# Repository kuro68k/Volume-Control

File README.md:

# Volume-Control
USB volume control and companion app

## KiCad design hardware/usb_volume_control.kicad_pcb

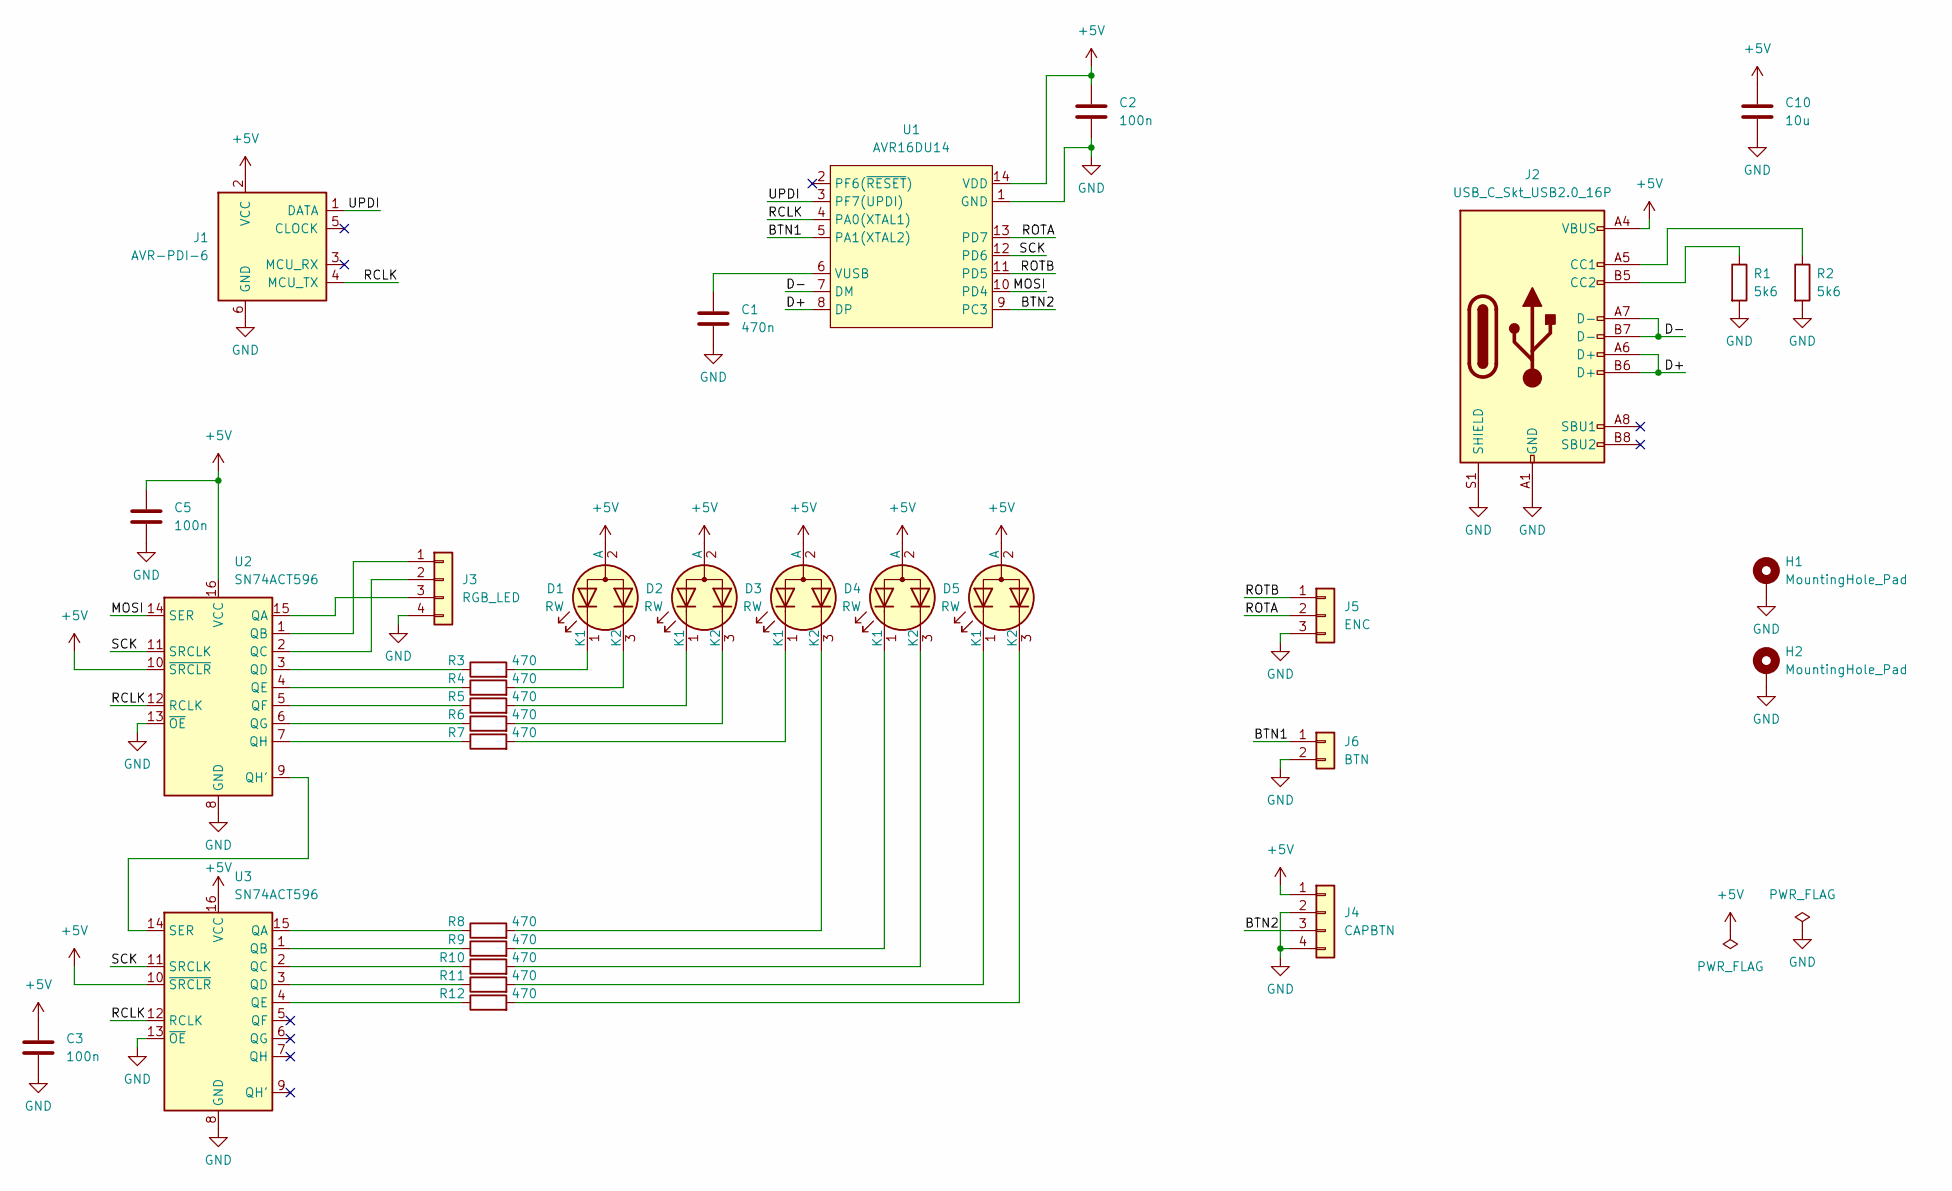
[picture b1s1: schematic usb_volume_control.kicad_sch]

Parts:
C1: 470n; C_0805_2012Metric_Pad1.18x1.45mm_HandSolder
C2, C3, C5: 100n; C_0805_2012Metric_Pad1.18x1.45mm_HandSolder
C10: 10u; C_0805_2012Metric_Pad1.18x1.45mm_HandSolder
D1, D2, D3, D4, D5: RW; LED_D3.0mm-3
H1, H2: MountingHole_Pad; MountingBracket_3.2mm_M3_Pad_tall
J1: AVR-PDI-6; PinHeader_2x03_P2.54mm_Vertical
J2: USB_C_Skt_USB2.0_16P; USB_C_Receptacle_GCT_USB4105-xx-A_16P_TopMnt_Horizontal
J3: RGB_LED; PinHeader_1x04_P2.54mm_Vertical
J4: CAPBTN; PinHeader_1x04_P2.54mm_Vertical
J5: ENC; PinHeader_1x03_P2.54mm_Vertical
J6: BTN; PinHeader_1x02_P2.54mm_Vertical
R1, R2: 5k6; R_0805_2012Metric_Pad1.20x1.40mm_HandSolder
R3, R4, R5, R6, R7, R8, R9, R10, R11, R12: 470; R_0805_2012Metric_Pad1.20x1.40mm_HandSolder
U1: AVR16DU14; SOIC-14_3.9x8.7mm_P1.27mm
U2, U3: SN74ACT596; TSSOP-16_4.4x5mm_P0.65mm

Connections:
+5V: C2.1, C3.1, C5.1, C10.1, D1.2 (A), D2.2 (A), D3.2 (A), D4.2 (A), D5.2 (A), J1.2 (VCC), J2.A4 (VBUS), J2.A9 (VBUS), J2.B4 (VBUS), J2.B9 (VBUS), J4.1, U1.14 (VDD), U2.10 (~SRCLR), U2.16 (VCC), U3.10 (~SRCLR), U3.16 (VCC)
/BTN1: J6.1, U1.5 (PA1(XTAL2))
/BTN2: J4.3, U1.9 (PC3)
/D+: J2.A6 (D+), J2.B6 (D+), U1.8 (DP)
/D-: J2.A7 (D-), J2.B7 (D-), U1.7 (DM)
/MOSI: U1.10 (PD4), U2.14 (SER)
/RCLK: J1.4 (MCU_TX), U1.4 (PA0(XTAL1)), U2.12 (RCLK), U3.12 (RCLK)
/ROTA: J5.2, U1.13 (PD7)
/ROTB: J5.1, U1.11 (PD5)
/SCK: U1.12 (PD6), U2.11 (SRCLK), U3.11 (SRCLK)
/UPDI: J1.1 (DATA), U1.3 (PF7(UPDI))
GND: C1.2, C2.2, C3.2, C5.2, C10.2, H1.1, H2.1, J1.6 (GND), J2.A1 (GND), J2.A12 (GND), J2.B1 (GND), J2.B12 (GND), J2.S1 (SHIELD), J3.4, J4.2, J4.4, J5.3, J6.2, R1.2, R2.2, U1.1 (GND), U2.8 (GND), U2.13 (~OE), U3.8 (GND), U3.13 (~OE)
unnamed: D1.1 (K1), R3.2
unnamed: D1.3 (K2), R4.2
unnamed: D2.1 (K1), R5.2
unnamed: D2.3 (K2), R6.2
unnamed: D3.1 (K1), R7.2
unnamed: D3.3 (K2), R8.2
unnamed: D4.1 (K1), R9.2
unnamed: D4.3 (K2), R10.2
unnamed: D5.1 (K1), R11.2
unnamed: D5.3 (K2), R12.2
unnamed: J2.A5 (CC1), R2.1
unnamed: J2.B5 (CC2), R1.1
unnamed: J3.1, U2.1 (QB)
unnamed: J3.2, U2.2 (QC)
unnamed: J3.3, U2.15 (QA)
unnamed: C1.1, U1.6 (VUSB)
unnamed: R3.1, U2.3 (QD)
unnamed: R4.1, U2.4 (QE)
unnamed: R5.1, U2.5 (QF)
unnamed: R6.1, U2.6 (QG)
unnamed: U2.9 (QH'), U3.14 (SER)
unnamed: R7.1, U2.7 (QH)
unnamed: R8.1, U3.15 (QA)
unnamed: R9.1, U3.1 (QB)
unnamed: R10.1, U3.2 (QC)
unnamed: R11.1, U3.3 (QD)
unnamed: R12.1, U3.4 (QE)

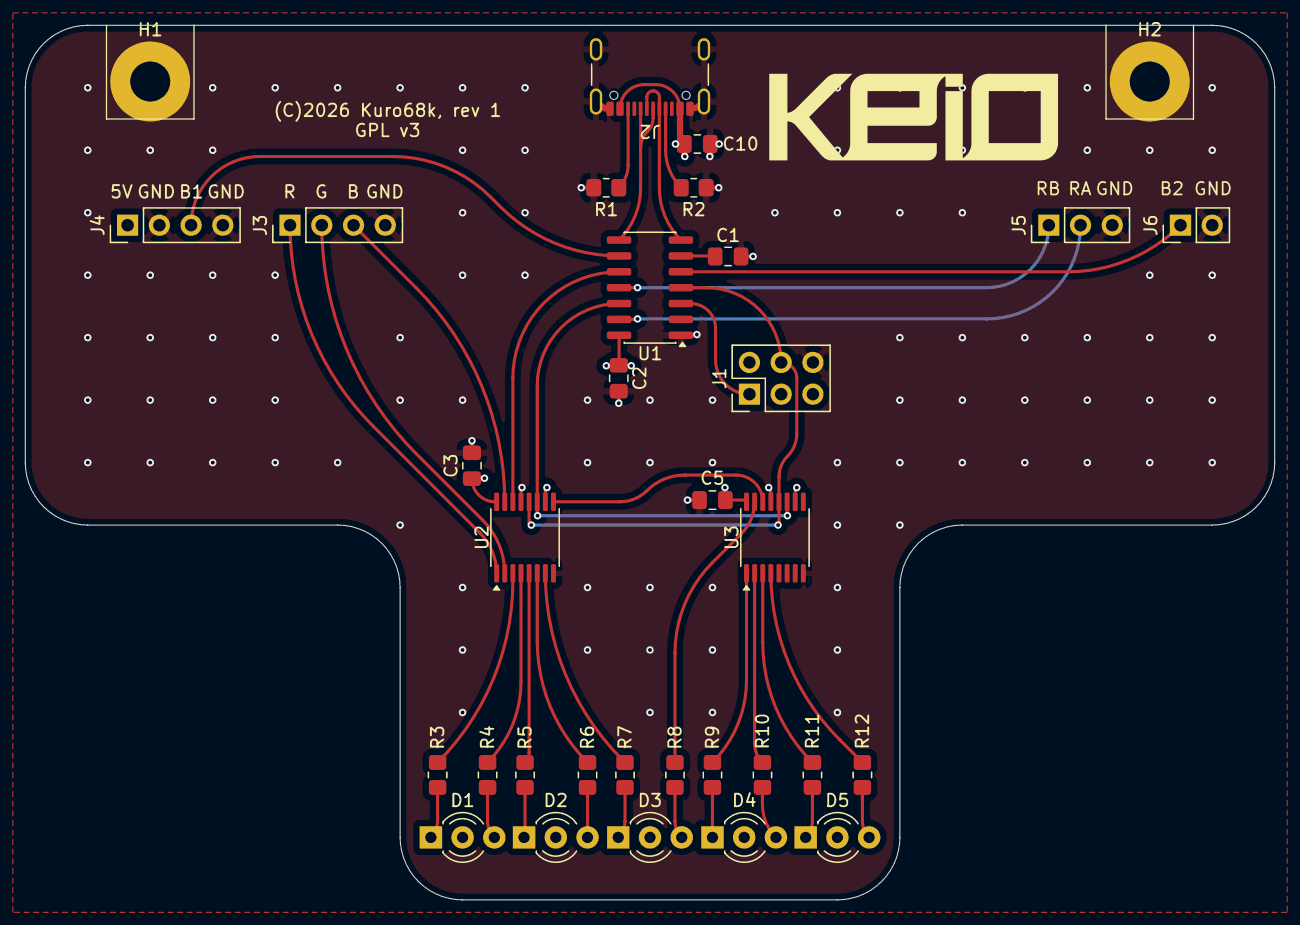
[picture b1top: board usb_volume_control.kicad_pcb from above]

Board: 4 copper layers, 100.0 x 70.0 mm, 33 parts (0 on the bottom side), 39 nets.

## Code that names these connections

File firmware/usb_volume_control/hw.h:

/*
 * hw.h
 *
 */ 


#ifndef HW_H_
#define HW_H_


#define BTN1_PORT		PORTA
#define BTN1_PIN_bm		PIN1_bm
#define BTN2_PORT		PORTC
#define BTN2_PIN_bm		PIN3_bm

#define RCLK_PORT		PORTA
#define RCLK_PIN_bm		PIN0_bm
#define SCK_PORT		PORTD
#define SCK_PIN_bm		PIN6_bm
#define MOSI_PORT		PORTD
#define MOSI_PIN_bm		PIN4_bm

#define ROTA_PORT		PORTD
#define ROTA_VPORT		VPORTD
#define ROTA_PIN_bm		PIN7_bm
#define ROTB_PORT		PORTD
#define ROTB_VPORT		VPORTD
#define ROTB_PIN_bm		PIN5_bm


extern void HW_init(void);


#endif /* HW_H_ */

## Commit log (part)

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2026-02-13 Finished PCB and imported to FreeCAD
2026-02-25 Rev 1 production files

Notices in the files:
hardware/usb_volume_control.kicad_pcb:
(C)2026 Kuro68k, rev 1
GPL v3
